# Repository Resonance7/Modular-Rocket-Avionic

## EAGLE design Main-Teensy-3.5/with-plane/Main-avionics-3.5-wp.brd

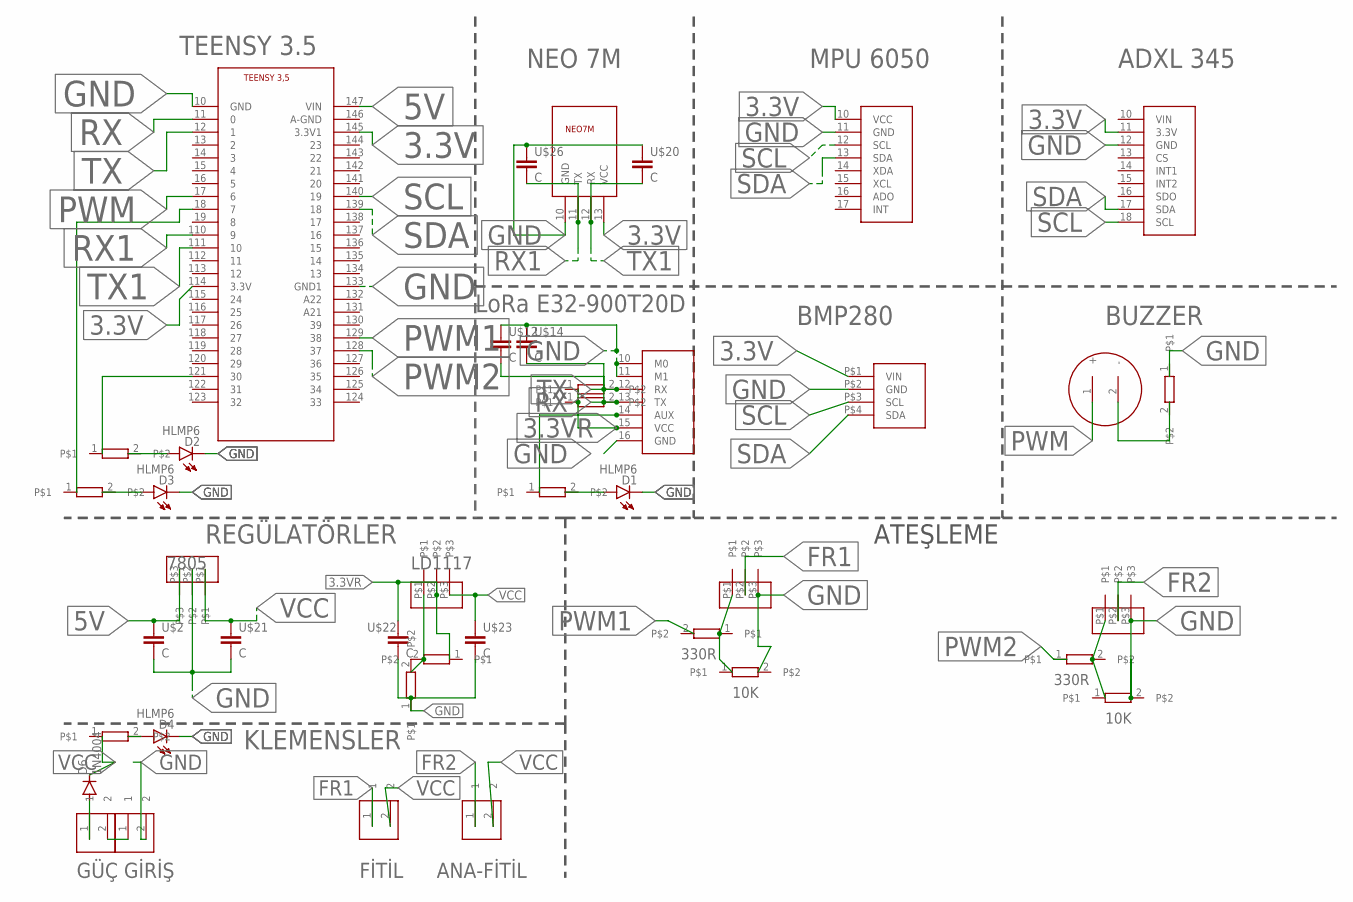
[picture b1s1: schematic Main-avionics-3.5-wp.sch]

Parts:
1K, 10R, 10R1, 10R2, 10R3, 10R4, 10R5, 10R6, 10R7, 10R8: R; 0204/7
D1, D2, D3, D4: HLMP6
D6: 1N4004; DO41-10
U$1: ADXL345
U$2, U$12, U$14, U$20, U$21, U$22, U$23, U$26: C; C075-032X103
U$3: BUZZEER; BUZZER
U$4, U$5, U$7, U$16: KLEMENS
U$6: BMP280
U$8: NEO7M
U$9, U$19, U$24, U$25: REGULATOR
U$10: LORA
U$11: TEENSY
U$13: MPU6050
U$15, U$17, U$18: R; 0204/7

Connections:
3.3V: U$1.11 (3.3V), U$6.P$1 (VIN), U$8.13 (VCC), U$11.114 (3.3V), U$11.145 (3.3V1), U$13.10 (VCC)
3.3VR: 10R1.1, 10R2.1, 10R4.1, U$10.15 (VCC), U$22.1, U$24.P$2
5V: U$2.1, U$11.147 (VIN), U$19.P$3
FR1: U$4.1, U$25.P$2
FR2: U$7.1, U$9.P$2
GND: 10R.2, 10R5.1, D1.K, D2.K, D3.K, D4.K, U$1.12 (GND), U$2.2, U$6.P$2 (GND), U$8.10 (GND), U$9.P$3, U$10.10 (M0), U$10.11 (M1), U$10.16 (GND), U$11.10 (GND), U$11.133 (GND1), U$12.1, U$13.11 (GND), U$14.1, U$15.1, U$16.2, U$18.2, U$19.P$2, U$20.1, U$21.2, U$22.2, U$23.2, U$25.P$3, U$26.1
unnamed: U$3.2 (-), U$15.2
unnamed: U$9.P$1, U$17.2, U$18.1
unnamed: 10R3.2, D1.A
unnamed: 10R3.1, U$10.14 (AUX)
unnamed: D6.A, U$5.1
unnamed: 1K.1, 10R.1, U$25.P$1
unnamed: U$5.2, U$16.1
unnamed: 10R6.2, D2.A
unnamed: 10R6.1, U$11.121 (30)
unnamed: 10R7.2, D3.A
unnamed: 10R7.1, U$11.18 (7)
unnamed: 10R8.2, D4.A
PWM: U$3.1 (+), U$11.17 (6)
PWM1: 1K.2, U$11.129 (38)
PWM2: U$11.128 (37), U$17.1
RX: 10R2.2, U$10.13 (TX), U$11.11 (0), U$12.2
RX1: U$8.11 (TX), U$11.110 (9), U$26.2
SCL: U$1.18 (SCL), U$6.P$3 (SCL), U$11.140 (19), U$13.12 (SCL)
SDA: U$1.17 (SDA), U$6.P$4 (SDA), U$11.139 (18), U$13.13 (SDA)
T: 10R4.2, 10R5.2, U$24.P$1
TX: 10R1.2, U$10.12 (RX), U$11.12 (1), U$14.2
TX1: U$8.12 (RX), U$11.111 (10), U$20.2
VCC: 10R8.1, D6.C, U$4.2, U$7.2, U$19.P$1, U$21.1, U$23.1, U$24.P$3

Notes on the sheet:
GÜÇ GİRİŞ
MPU 6050
LoRa E32-900T20D
BUZZER
BMP280
7805
LD1117
ATEŞLEME
ADXL 345
NEO 7M
TEENSY 3.5
REGÜLATÖRLER
KLEMENSLER
10K
330R
FİTİL
ANA-FİTİL

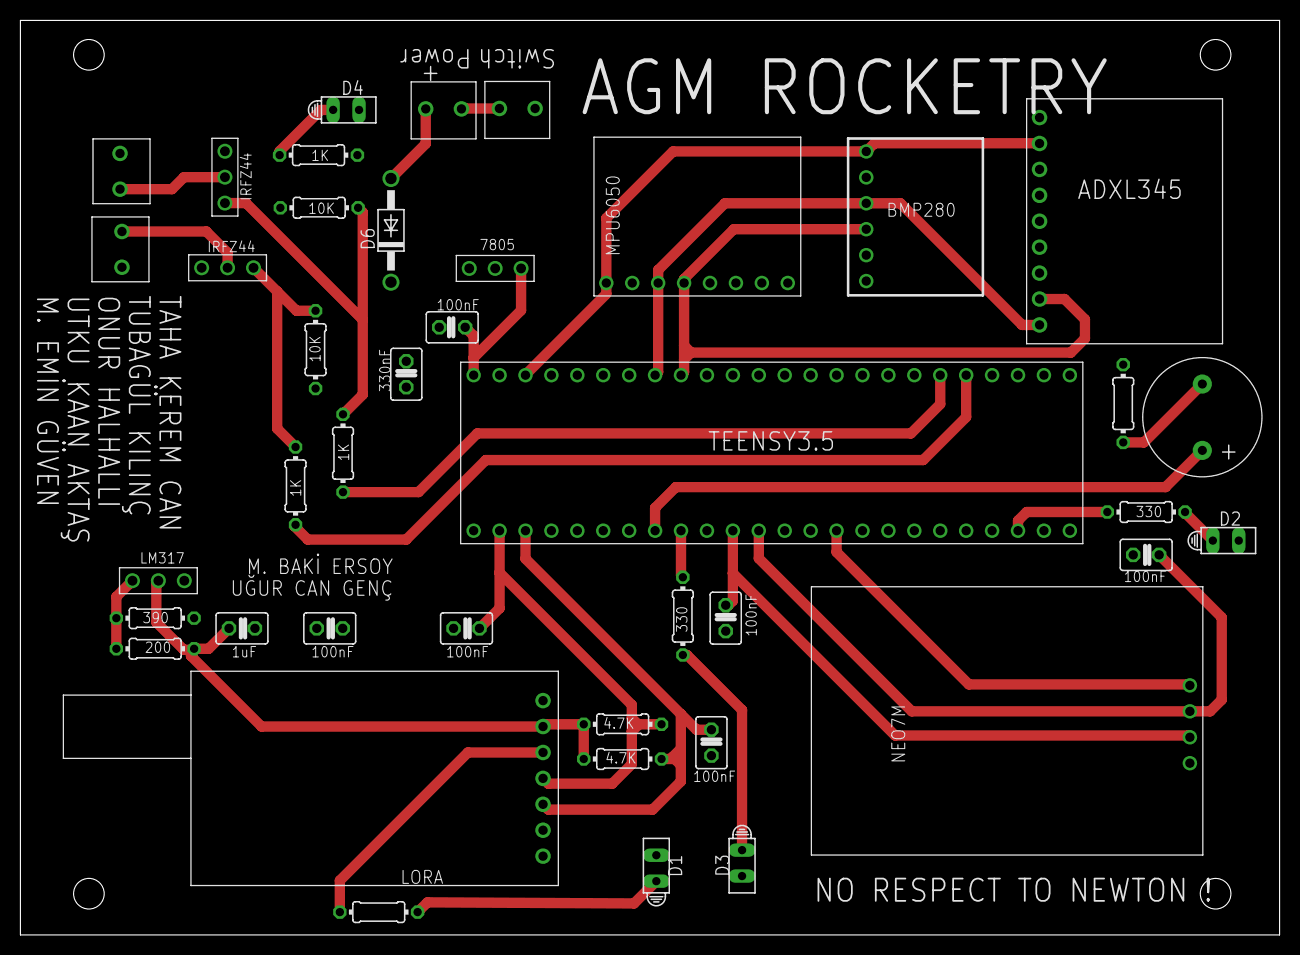
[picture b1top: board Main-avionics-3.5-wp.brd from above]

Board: 2 copper layers, 123.4 x 89.6 mm, 41 parts (0 on the bottom side), 29 nets.
